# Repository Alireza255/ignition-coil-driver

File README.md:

# Simple & Affordable Ignition Coil Driver

This repo provides a simple, affordable ignition coil driver circuit, ideal for hobbyists experimenting with high-voltage.  It's easy to build using readily available parts.

## Features

* Cost-effective & easy to implement.
* Complete with schematics, layout, & component list.

## Circuit & PCB

[Circuit Diagram Image]
[PCB Layout Image (Top & Bottom)]

## Build & Use
1. Make the PCB
1. Solder components per the diagram/layout.
2. Connect ignition coil.
3. Don't leave the output of the ignition coil flap around in the breeze! Place it near the ground of the coil.
4. Connect power supply to observe sparks
   
## **WARNING: High Voltage!**
This circuit is dangerous.  Exercise caution.  Do not touch when powered.  Proper insulation is crucial.  Seek expert help if needed.

## Disclaimer
This project is provided as-is, without any warranty. The author is not responsible for any damage or injury resulting from the use or misuse of this design.  Use at your own risk.

## Contribute
Contributions are welcome! Submit pull requests.

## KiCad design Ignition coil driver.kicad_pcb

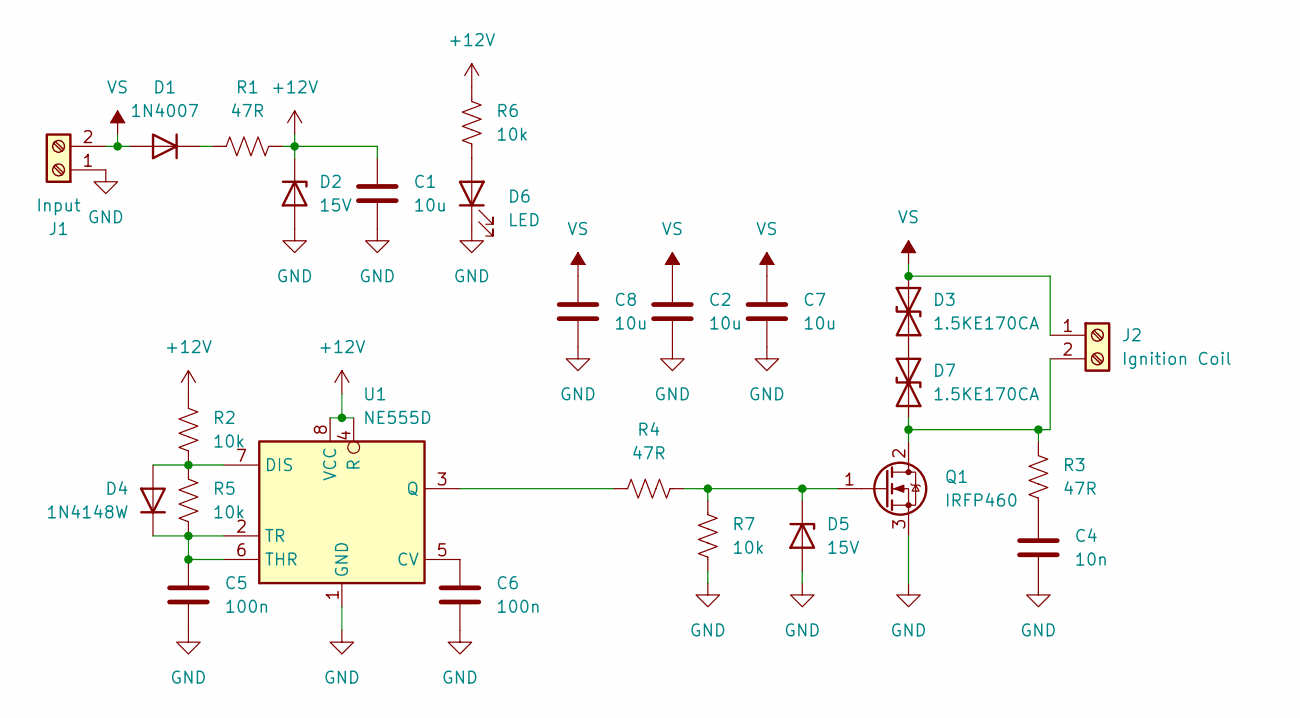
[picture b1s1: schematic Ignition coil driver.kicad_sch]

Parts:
C1, C2, C7, C8: 10u; C_1206_3216Metric
C4: 10n; C_Disc_D11.0mm_W5.0mm_P7.50mm
C5, C6: 100n; C_1206_3216Metric
D1: 1N4007; D_SMA
D2, D5: 15V; D_MiniMELF
D3, D7: 1.5KE170CA; D_DO-201AE_P3.81mm_Vertical_AnodeUp
D4: 1N4148W; D_SOD-123
D6: LED; LED_D5.0mm
J1: Input; TerminalBlock_Philmore_TB132_1x02_P5.00mm_Horizontal
J2: Ignition Coil; TerminalBlock_Philmore_TB132_1x02_P5.00mm_Horizontal
Q1: IRFP460; TO-247-3_Vertical
R1, R4: 47R; R_1206_3216Metric
R2, R5, R6, R7: 10k; R_1206_3216Metric
R3: 47R; R_Axial_DIN0207_L6.3mm_D2.5mm_P7.62mm_Horizontal
U1: NE555D; SOIC-8_3.9x4.9mm_P1.27mm

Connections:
+12V: C1.1, D2.1 (K), R1.2, R2.1, R6.1, U1.4 (R), U1.8 (VCC)
GND: C1.2, C2.2, C4.2, C5.2, C6.2, C7.2, C8.2, D2.2 (A), D5.2 (A), D6.1 (K), J1.1, Q1.3 (S), R7.2, U1.1 (GND)
unnamed: C4.1, R3.2
unnamed: D1.1 (K), R1.1
unnamed: D3.1 (A1), D7.2 (A2)
unnamed: D4.2 (A), R2.2, R5.1, U1.7 (DIS)
unnamed: C5.1, D4.1 (K), R5.2, U1.2 (TR), U1.6 (THR)
unnamed: D5.1 (K), Q1.1 (G), R4.2, R7.1
unnamed: D6.2 (A), R6.2
unnamed: D7.1 (A1), J2.2, Q1.2 (D), R3.1
unnamed: C6.1, U1.5 (CV)
unnamed: R4.1, U1.3 (Q)
VS: C2.1, C7.1, C8.1, D1.2 (A), D3.2 (A2), J1.2, J2.1

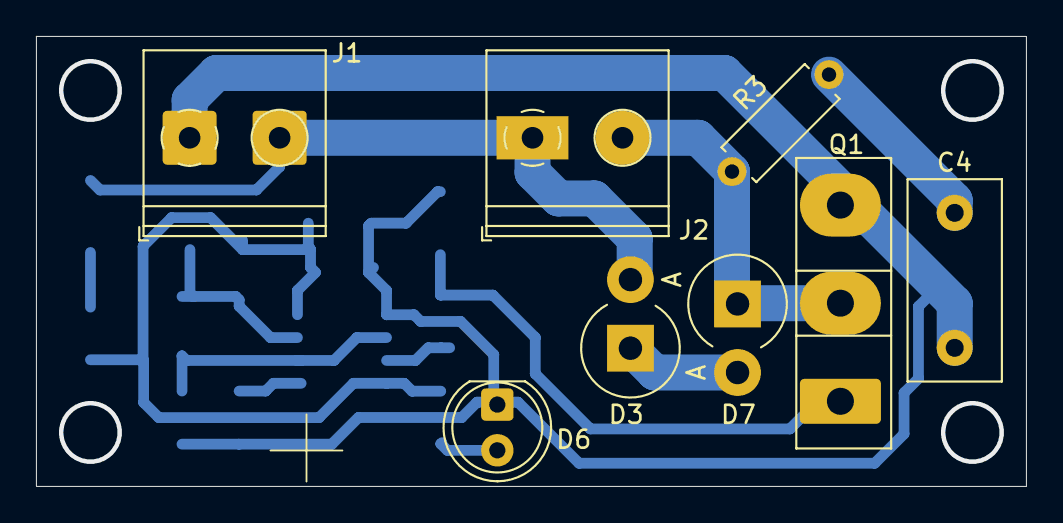
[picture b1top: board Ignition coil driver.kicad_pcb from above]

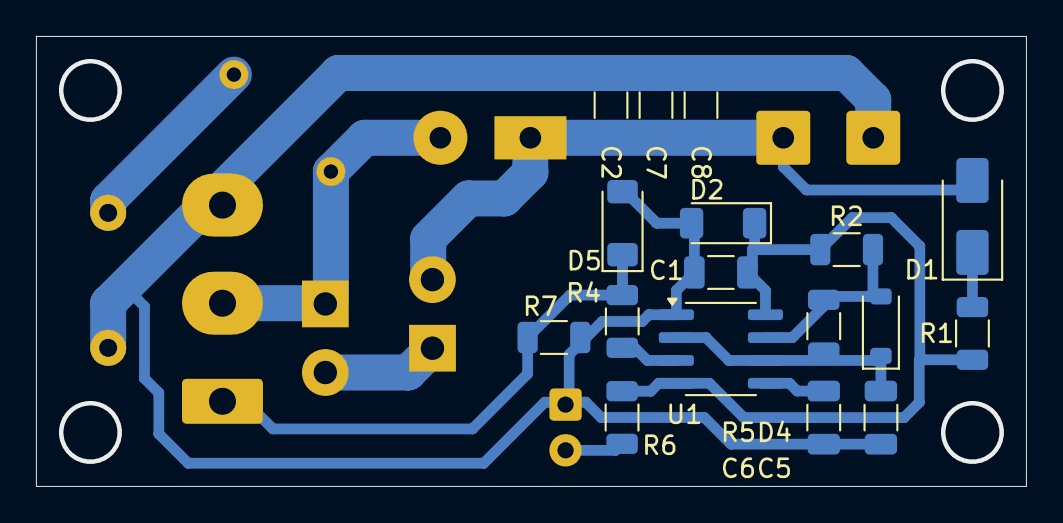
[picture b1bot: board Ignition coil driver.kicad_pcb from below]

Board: 2 copper layers, 55.0 x 25.0 mm, 25 parts (17 on the bottom side), 13 nets.

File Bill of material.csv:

Reference,Value,Datasheet,Footprint,Qty,DNP
"C1,C2,C7,C8",10u,~,Capacitor_SMD:C_1206_3216Metric,4,
C4,10n,~,Capacitor_THT:C_Disc_D11.0mm_W5.0mm_P7.50mm,1,
"C5,C6",100n,~,Capacitor_SMD:C_1206_3216Metric,2,
D1,1N4007,~,Diode_SMD:D_SMA,1,
"D2,D5",15V,~,Diode_SMD:D_MiniMELF,2,
"D3,D7",1.5KE170CA,https://www.vishay.com/docs/88301/15ke.pdf,Diode_THT:D_DO-201AE_P3.81mm_Vertical_AnodeUp,2,
D4,1N4148W,https://www.vishay.com/docs/85748/1n4148w.pdf,Diode_SMD:D_SOD-123,1,
D6,LED,~,LED_THT:LED_D5.0mm,1,
J1,Input,~,TerminalBlock_Philmore:TerminalBlock_Philmore_TB132_1x02_P5.00mm_Horizontal,1,
J2,Ignition Coil,~,TerminalBlock_Philmore:TerminalBlock_Philmore_TB132_1x02_P5.00mm_Horizontal,1,
Q1,IRFP460,,Package_TO_SOT_THT:TO-247-3_Vertical,1,
"R1,R3,R4",47R,~,-- mixed values --,3,
"R2,R5,R6,R7",10k,~,Resistor_SMD:R_1206_3216Metric,4,
U1,NE555D,http://www.ti.com/lit/ds/symlink/ne555.pdf,Package_SO:SOIC-8_3.9x4.9mm_P1.27mm,1,

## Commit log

2025-02-22 Uploaded the main files.
